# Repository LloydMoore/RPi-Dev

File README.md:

RPi-Dev
=======
The RPi-DEV board is designed to be a flexible development
and prototyping platform for both the Raspberry Pi and PSoC
ecosystems. The board has the functionality needed for real
time embedded projects. The heart of the board is a Cypress
PSoC  processor allowing user programmable analog and digital
circuitry based on the target project. The board has 8
high current drivers which form a configurable motor 
controller, RS-232/485 driver, 3 Diligent PMOD connectors,
and 18 additional I/O.

Root Directory Map:
=======
BotMonitor : Sample code for the Raspberry Pi GUI demo application
BotPsoc : Sample code for the PSoC5LP demo application
Common : Sample code which is common to multiple applications
doc : Documentation for the project
pcb : Schematics and PCB files for the project
LICENSE : License file for the sample code
README.md : This file

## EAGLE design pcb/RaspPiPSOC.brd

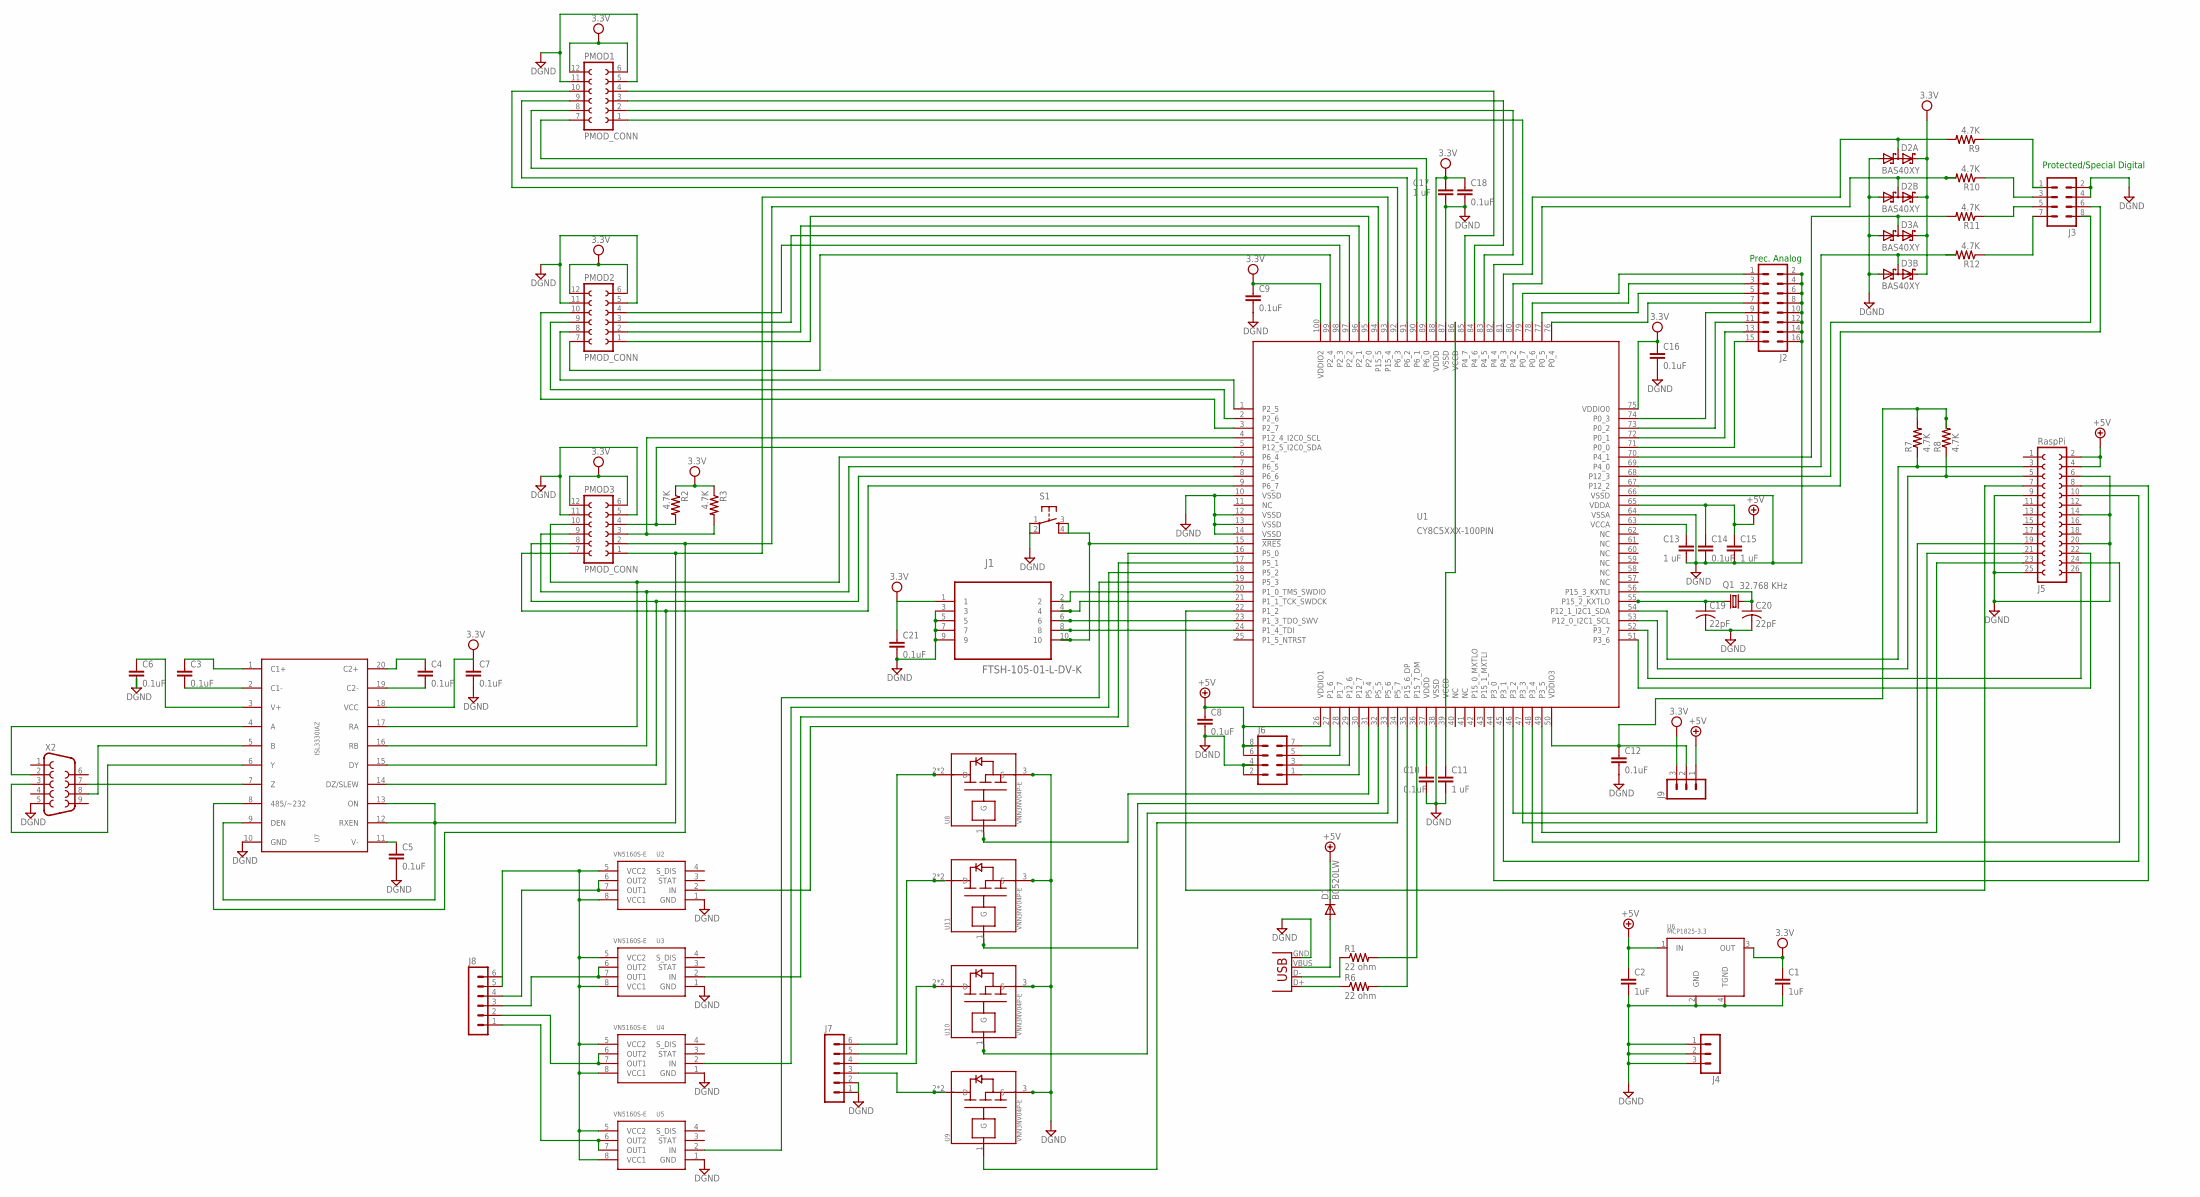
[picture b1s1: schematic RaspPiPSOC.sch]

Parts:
C1, C2: 1uF; C0805
C3, C4, C5, C6, C7, C8, C9, C10, C12, C14, C16, C18, C21: 0.1uF; C0805
C11, C13, C15, C17: 1 uF; C0805
C19, C20: 22pF; C0805
D1: B0520LW; SOD-123_MINI-SMA
D2, D3: BAS40XY; SOT363_PHILIPS
J1: FTSH-105-01-L-DV-K; SAMTEC_FTSH-105-01-L-DV-K
J2: MA08-2
J3, J6: MA04-2
J4, J9: MA03-1
J5: RaspPi; FE13-2
J7, J8: MA06-1
PMOD1, PMOD2, PMOD3: PMOD_CONN
Q1: 32.768 KHz; TC26H
R1, R6: 22 ohm; R0805
R2, R3, R7, R8, R9, R10, R11, R12: 4.7K; R0805
S1: TAC_SWITCHSMD; TACTILE_SWITCH_SMD
U1: CY8C5XXX-100PIN; TQFP-14X14-100
U2, U3, U4, U5: VN5160S-E; SOIC8
U6: MCP1825-3.3; SOT223
U7: ISL3330IAZ; SSOP20
U8, U9, U10, U11: VNN3NV04P-E; SOT223
X1: USBSMD; USB-MINIB
X2: DB9

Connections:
+5V: C2.1, C8.1, C14.1, C15.1, D1.C, J5.2, J5.4, J6.6, J6.8, J9.1, U1.26 (VDDIO1), U1.65 (VDDA), U6.1 (IN)
DGND: C1.2, C2.2, C5.2, C6.2, C7.2, C8.2, C9.2, C10.2, C11.2, C12.2, C13.2, C14.2, C15.2, C16.2, C17.2, C18.2, C19.2, C20.2, C21.2, D2.1 (A1), D2.4 (A1), D3.1 (A1), D3.4 (A1), J1.3, J1.5, J1.7, J1.9, J2.2, J2.4, J2.6, J2.8, J2.10, J2.12, J2.14, J2.16, J3.2, J3.4, J4.1, J4.2, J4.3, J5.6, J5.9, J5.14, J5.20, J5.25, J6.2, J6.4, J7.1, J7.2, PMOD1.5, PMOD1.11, PMOD2.5, PMOD2.11, PMOD3.5, PMOD3.11, S1.1, S1.2, U1.10 (VSSD), U1.12 (VSSD), U1.13 (VSSD), U1.14 (VSSD), U1.38 (VSSD), U1.64 (VSSA), U1.66 (VSSD), U1.87 (VSSD), U2.1 (GND), U3.1 (GND), U4.1 (GND), U5.1 (GND), U6.2 (GND), U6.4 (TGND), U7.10 (GND), U8.3 (S), U9.3 (S), U10.3 (S), U11.3 (S), X1.GND, X2.5
unnamed: C12.1, J9.2, R7.2, R8.2, U1.50 (VDDIO3)
unnamed: PMOD3.10, U1.6 (P6_4), U7.17 (RA)
unnamed: J8.3, U3.6 (OUT2), U3.7 (OUT1)
unnamed: J8.2, U4.6 (OUT2), U4.7 (OUT1)
unnamed: J8.1, U5.6 (OUT2), U5.7 (OUT1)
unnamed: PMOD3.4, R2.2, U1.5 (P12_5_I2C0_SDA)
unnamed: PMOD3.3, R3.2, U1.4 (P12_4_I2C0_SCL)
unnamed: C20.1, Q1.1, U1.56 (P15_3_KXTLI)
unnamed: C19.1, Q1.2, U1.55 (P15_2_KXTLO)
unnamed: J5.7, U1.22 (P1_2)
unnamed: PMOD3.2, U1.94 (P15_5), U7.8 (485/~232)
unnamed: PMOD3.8, U1.8 (P6_6), U7.15 (DY)
unnamed: PMOD2.1, U1.95 (P2_0)
unnamed: PMOD2.2, U1.96 (P2_1)
unnamed: PMOD2.3, U1.97 (P2_2)
unnamed: PMOD2.4, U1.98 (P2_3)
unnamed: PMOD2.7, U1.99 (P2_4)
unnamed: PMOD2.8, U1.1 (P2_5)
unnamed: C11.1, U1.39 (VCCD), U1.86 (VCCD)
unnamed: PMOD2.9, U1.2 (P2_6)
unnamed: PMOD2.10, U1.3 (P2_7)
unnamed: PMOD1.3, U1.84 (P4_6)
unnamed: PMOD1.10, U1.92 (P6_3)
unnamed: C10.1, U1.37 (VDDD)
unnamed: C13.1, U1.63 (VCCA)
unnamed: PMOD1.9, U1.91 (P6_2)
unnamed: PMOD1.8, U1.90 (P6_1)
unnamed: PMOD1.7, U1.89 (P6_0)
unnamed: J5.19, U1.46 (P3_2)
unnamed: PMOD1.1, U1.82 (P4_4)
unnamed: PMOD1.2, U1.83 (P4_5)
unnamed: PMOD1.4, U1.85 (P4_7)
unnamed: J5.22, U1.51 (P3_6)
unnamed: J5.26, U1.52 (P3_7)
unnamed: C4.1, U7.20 (C2+)
unnamed: C4.2, U7.19 (C2-)
unnamed: C3.2, U7.2 (C1-)
unnamed: C6.1, U7.3 (V+)
unnamed: C3.1, U7.1 (C1+)
unnamed: C5.1, U7.11 (V-)
unnamed: U7.4 (A), X2.2
unnamed: U7.6 (Y), X2.3
unnamed: U7.5 (B), X2.8
unnamed: U7.7 (Z), X2.7
unnamed: PMOD3.9, U1.7 (P6_5), U7.16 (RB)
unnamed: R6.1, X1.D+
unnamed: R1.1, X1.D-
unnamed: R6.2, U1.35 (P15_6_DP)
unnamed: R1.2, U1.36 (P15_7_DM)
unnamed: J5.21, U1.47 (P3_3)
unnamed: J5.23, U1.49 (P3_5)
unnamed: J5.24, U1.48 (P3_4)
unnamed: J5.8, U1.44 (P3_0)
unnamed: J5.10, U1.45 (P3_1)
unnamed: PMOD3.1, U1.93 (P15_4), U7.9 (DEN), U7.12 (RXEN), U7.13 (ON)
unnamed: PMOD3.7, U1.9 (P6_7), U7.14 (DZ/SLEW)
unnamed: D1.A, X1.VBUS
unnamed: J1.10, S1.3, S1.4, U1.15 (!XRES!)
unnamed: J5.3, R7.1, U1.54 (P12_1_I2C1_SDA)
unnamed: J1.2, U1.20 (P1_0_TMS_SWDIO)
unnamed: J1.4, U1.21 (P1_1_TCK_SWDCK)
unnamed: J1.8, U1.24 (P1_4_TDI)
unnamed: J1.6, U1.23 (P1_3_TDO_SWV)
unnamed: J5.5, R8.1, U1.53 (P12_0_I2C1_SCL)
unnamed: J2.1, U1.79 (P0_7)
unnamed: J2.3, U1.78 (P0_6)
unnamed: J2.5, U1.77 (P0_5)
unnamed: J2.7, U1.76 (P0_4)
unnamed: J2.9, U1.74 (P0_3)
unnamed: J2.11, U1.73 (P0_2)
unnamed: J2.13, U1.72 (P0_1)
unnamed: J2.15, U1.71 (P0_0)
unnamed: D2.6 (C1A2), R9.2, U1.81 (P4_3)
unnamed: D2.3 (C1A2), R10.2, U1.80 (P4_2)
unnamed: D3.6 (C1A2), R11.2, U1.70 (P4_1)
unnamed: D3.3 (C1A2), R12.2, U1.69 (P4_0)
unnamed: J3.1, R9.1
unnamed: J3.7, R12.1
unnamed: J3.5, R11.1
unnamed: J3.3, R10.1
unnamed: U1.19 (P5_3), U5.2 (IN)
unnamed: U1.18 (P5_2), U4.2 (IN)
unnamed: J6.7, U1.27 (P1_6)
unnamed: J6.5, U1.28 (P1_7)
unnamed: J3.8, U1.68 (P12_3)
unnamed: J3.6, U1.67 (P12_2)
unnamed: J6.3, U1.29 (P12_6)
unnamed: J6.1, U1.30 (P12_7)
unnamed: U1.17 (P5_1), U3.2 (IN)
unnamed: U1.34 (P5_7), U9.1 (G)
unnamed: U1.33 (P5_6), U10.1 (G)
unnamed: U1.32 (P5_5), U11.1 (G)
unnamed: U1.31 (P5_4), U8.1 (G)
unnamed: U1.16 (P5_0), U2.2 (IN)
unnamed: J7.6, U8.2 (D), U8.4 (D)
unnamed: J7.5, U11.2 (D), U11.4 (D)
unnamed: J7.4, U10.2 (D), U10.4 (D)
unnamed: J8.4, U2.6 (OUT2), U2.7 (OUT1)
unnamed: J8.5, J8.6, U2.5 (VCC2), U2.8 (VCC1), U3.5 (VCC2), U3.8 (VCC1), U4.5 (VCC2), U4.8 (VCC1), U5.5 (VCC2), U5.8 (VCC1)
unnamed: J7.3, U9.2 (D), U9.4 (D)
VCC: C1.1, C7.1, C9.1, C16.1, C17.1, C18.1, C21.1, D2.2 (C2), D2.5 (C2), D3.2 (C2), D3.5 (C2), J1.1, J9.3, PMOD1.6, PMOD1.12, PMOD2.6, PMOD2.12, PMOD3.6, PMOD3.12, R2.1, R3.1, U1.75 (VDDIO0), U1.88 (VDDD), U1.100 (VDDIO2), U6.3 (OUT), U7.18 (VCC)

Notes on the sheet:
Protected/Special Digital
Prec. Analog

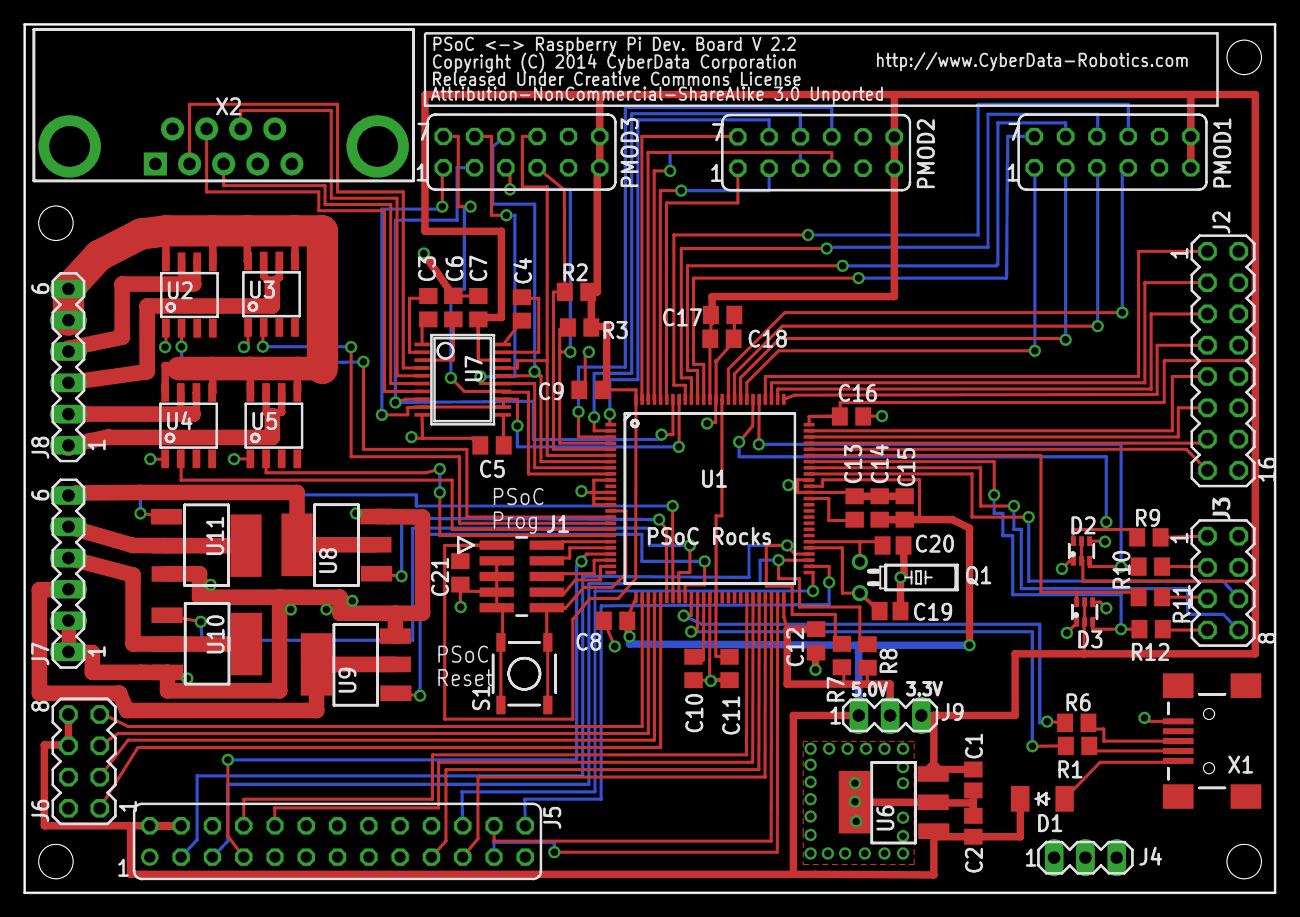
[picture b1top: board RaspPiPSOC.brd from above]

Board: 2 copper layers, 101.5 x 70.5 mm, 61 parts (1 on the bottom side), 103 nets.

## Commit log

2014-01-08 Check in of the updated README.md file
2014-01-08 Moving of documentation files into Git repository
2014-01-08 Moving of schematic and PCB files to Git repo
2014-01-08 Moving of applications into GitHub repo
2014-01-08 Updating directory structure
2014-01-08 Fixed build issue related to directory move
2014-01-09 Fix up of README.md to show better in browser
2014-01-09 Correction for directory restructuring
2014-01-09 Minor doc fixups
2014-01-20 Corrected C3 on BOM
2014-01-20 Added errata documentation for 32KHz oscillator issue
2014-01-21 Cleaned out a set of unnecessary files
2014-01-21 Added .gitignore file
2014-01-24 Updated driver reference numbers in PSoC schematic
    Motor driver IC references in PSoC schematic now match the parts on the
    PCB schematic
2014-02-19 Corrected DMA not running issue
    Corrected an issue where the DMA transfers for the SPI ring were not
    working correctly.
2014-02-19 Adding back "temp" files as they are needed
    In some cases PSoC creator is using some of these files and fails
    silently / builds incorrectly when something here is not present. It
    isn't clear specifically which files are the solution here so being safe
    and taking them all.

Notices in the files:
pcb/RaspPiPSOC.brd:
Copyright (C) 2014 CyberData Corporation
Released Under Creative Commons License
